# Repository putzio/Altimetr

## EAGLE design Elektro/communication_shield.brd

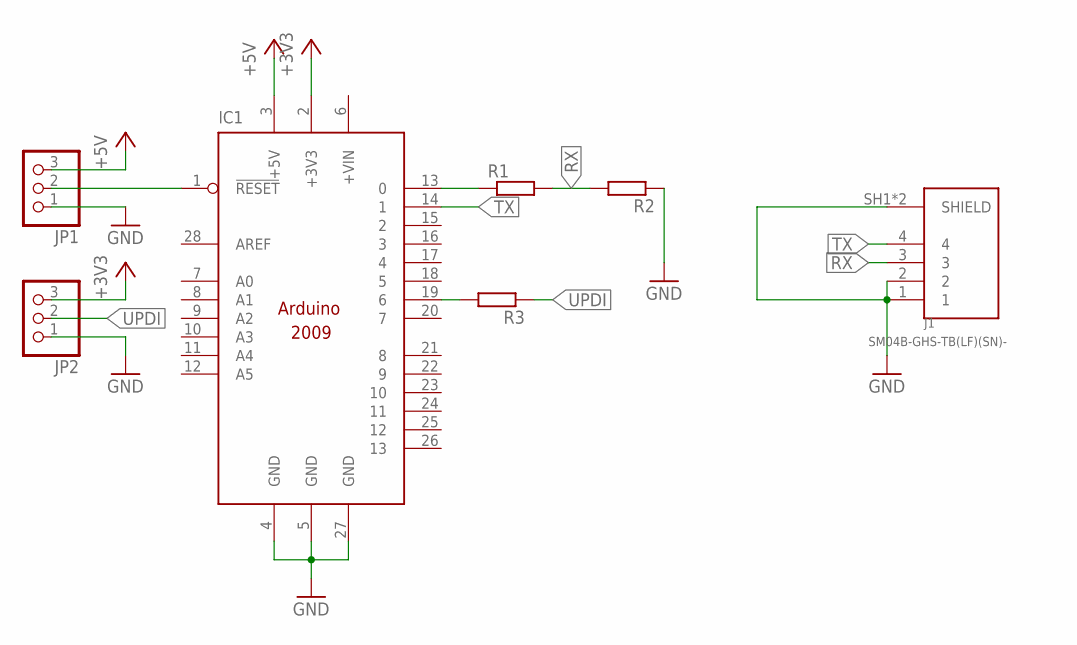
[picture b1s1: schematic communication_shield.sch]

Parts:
IC1: ARDUINO2009_10; ARDUINO2009
J1: SM04B-GHS-TB(LF)(SN)-; JST_SM04B-GHS-TB(LF)(SN)-
JP1, JP2: PINHD-1X3; 1X03
R1, R2, R3: R-EU_0204/7; 0204/7

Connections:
+3V3: IC1.2 (+3V3), JP2.3
+5V: IC1.3 (+5V), JP1.3
GND: IC1.4 (GND), IC1.5 (GND), IC1.27 (GND), J1.1, J1.2, J1.SH1 (SHIELD), J1.SH2 (SHIELD), JP1.1, JP2.1, R2.1
unnamed: IC1.19 (6), R3.2
unnamed: IC1.13 (0), R1.1
unnamed: IC1.1 (!RESET), JP1.2
RX: J1.3, R1.2, R2.2
TX: IC1.14 (1), J1.4
UPDI: JP2.2, R3.1

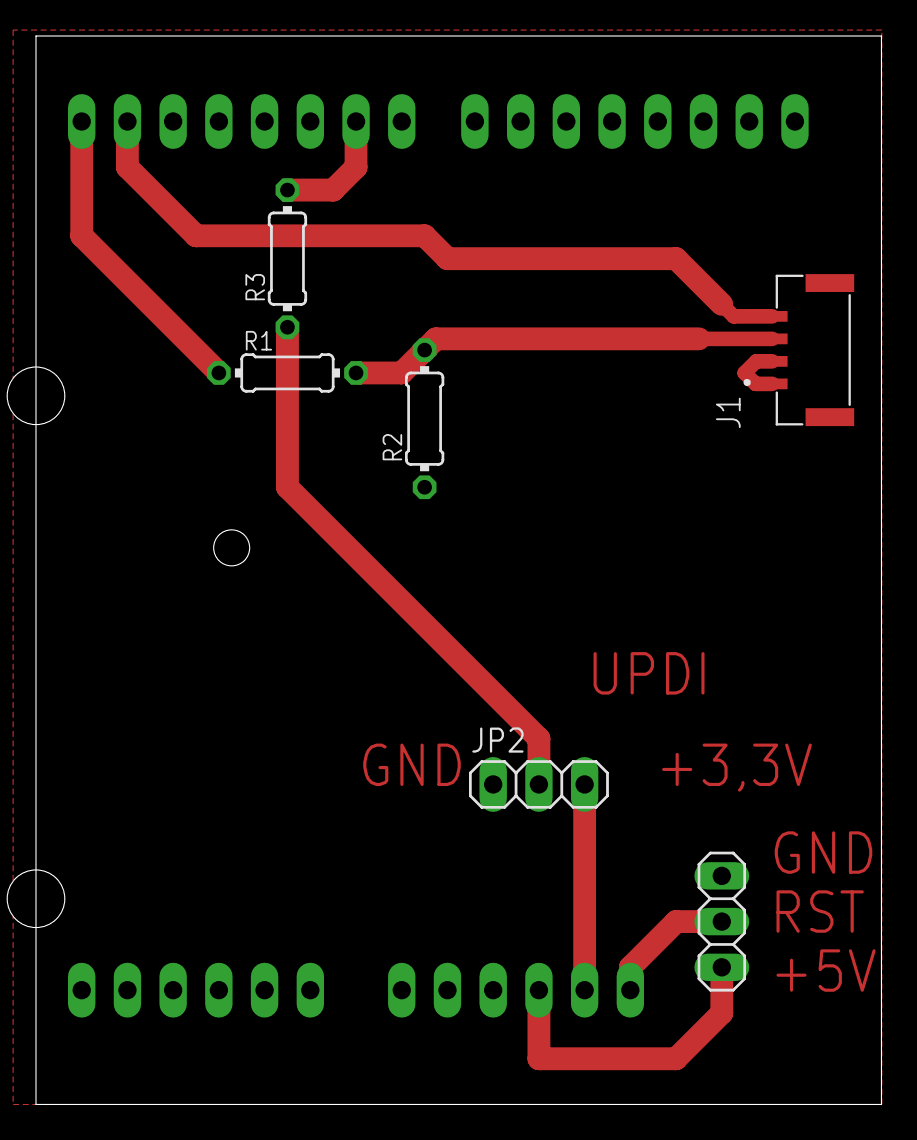
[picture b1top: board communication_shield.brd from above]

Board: 2 copper layers, 47.0 x 59.4 mm, 7 parts (1 on the bottom side), 9 nets.

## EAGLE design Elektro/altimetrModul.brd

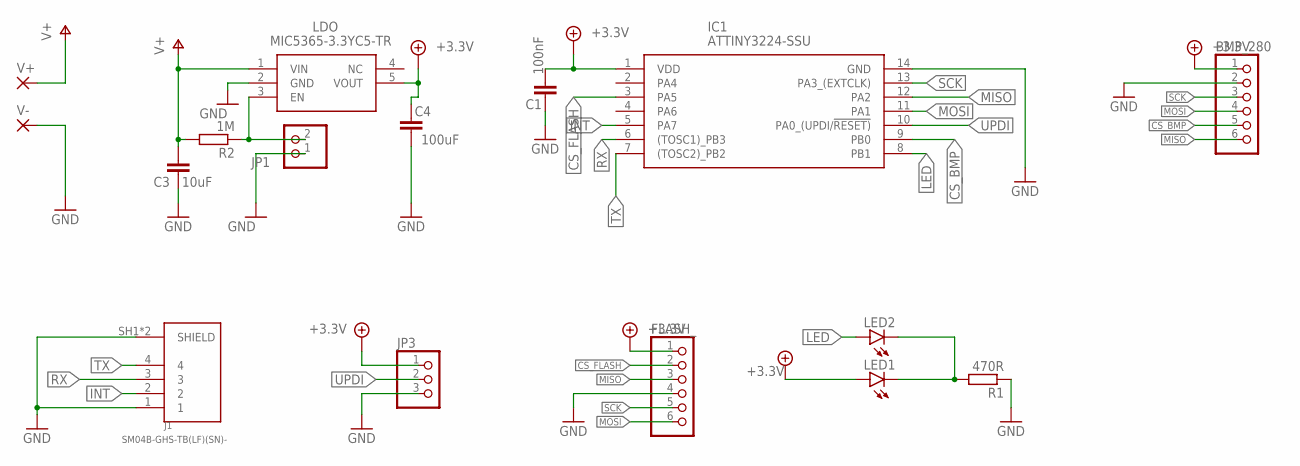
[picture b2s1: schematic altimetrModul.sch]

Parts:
BMP_280: PINHD-1X6; 1X06
C1: 100nF; C0805
C3: 10uF; C0805
C4: 100uF; C0805
FLASH_: PINHD-1X6; 1X06
IC1: ATTINY3224-SSU; SOIC127P600X175-14N
J1: SM04B-GHS-TB(LF)(SN)-; JST_SM04B-GHS-TB(LF)(SN)-
JP1: PINHD-1X2/90; 1X02/90
JP3: PINHD-1X3/90; 1X03/90
LDO: MIC5365-3.3YC5-TR; SOT65P210X110-5N
LED1, LED2: LEDCHIP-LED0805; CHIP-LED0805
R1: 470R; R0805
R2: 1M; R0805
V+: SMD2; SMD1,27-2,54
V-: SMD2; SMD1,27-2,54

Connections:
+3.3V: BMP_280.1, C1.1, C4.2, FLASH_.1, IC1.1 (VDD), JP3.1, LDO.5 (VOUT), LED1.A
CS_BMP: BMP_280.5, IC1.9 (PB0)
CS_FLASH: FLASH_.2, IC1.3 (PA5)
EN: JP1.2, LDO.3 (EN), R2.1
GND: BMP_280.2, C1.2, C3.1, C4.1, FLASH_.4, IC1.14 (GND), J1.1, J1.SH1 (SHIELD), J1.SH2 (SHIELD), JP1.1, JP3.3, LDO.2 (GND), R1.1, V-.1
INT: IC1.5 (PA7), J1.2
LED: IC1.8 (PB1), LED2.A
MISO: BMP_280.6, FLASH_.3, IC1.12 (PA2)
MOSI: BMP_280.4, FLASH_.6, IC1.11 (PA1)
unnamed: LED1.C, LED2.C, R1.2
RX: IC1.6 ((TOSC1)_PB3), J1.3
SCK: BMP_280.3, FLASH_.5, IC1.13 (PA3_(EXTCLK))
TX: IC1.7 ((TOSC2)_PB2), J1.4
UPDI: IC1.10 (PA0_(UPDI/!RESET)), JP3.2
V+: C3.2, LDO.1 (VIN), R2.2, V+.1

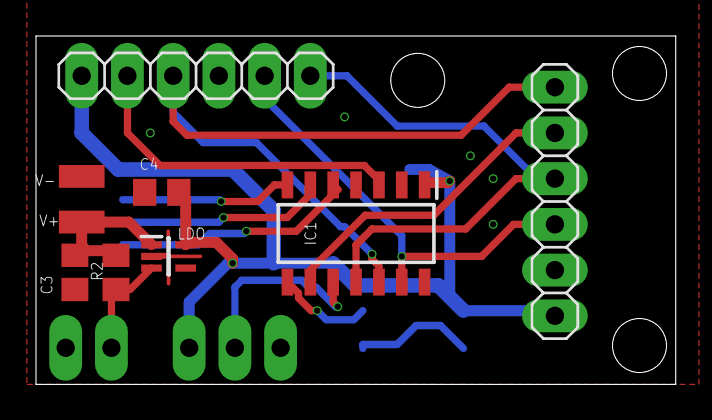
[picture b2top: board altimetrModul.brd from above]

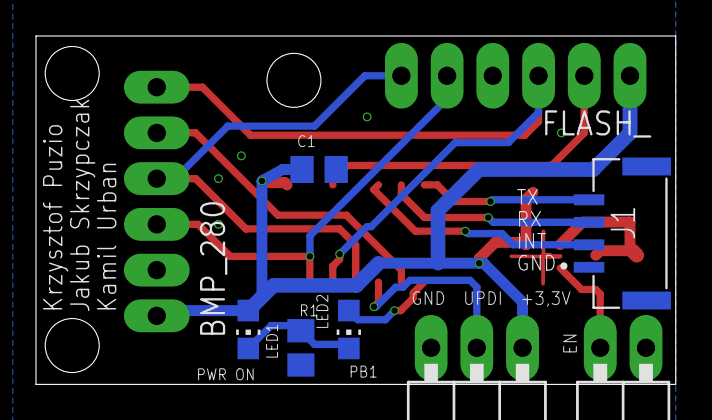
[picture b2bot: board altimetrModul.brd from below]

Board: 2 copper layers, 35.5 x 19.4 mm, 16 parts (7 on the bottom side), 15 nets.

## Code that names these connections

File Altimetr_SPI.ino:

//#include <Arduino.h>
//#include <SPI.h>
#include <avr/eeprom.h>
#include <Adafruit_BMP280.h>
#include <SPIMemory.h>
#include <SPI.h>
#include <avr/io.h>

// pinout
// CS -> write LOW to choose the salve
#define WRITE_PROTECTION 0  // WP - PA4
#define CS_FLASH 1          // PA5
#define SEND_DATA_UART_EN 3 // INT - PA7
#define RX 4                // PB3
#define TX 5                // PB2
#define LED 6               // PB1
#define CS_BMP 7            // PB0
#define UPDI 11             // PA0
#define MOSI 8              // PA1
#define MISO 9              // PA2
#define SCK 10              // PA3

#define SEA_LEVEL_HPA 1020.0
#define TIME_INTERVAL 1000 // ms
#define SEA_LEVEL_ADRESS 0x00 
#define START_ADRESS SEA_LEVEL_ADRESS

#define F_SPI 1000000 // 1 MHz -> the same frequency is required, so we take the lower one from BMP and set it to FLASH

SPIFlash *flash;
Adafruit_BMP280 bmp(CS_BMP, MOSI, MISO, SCK);

float initialHight;
uint64_t t = 0; // timer updated with millis()
bool flashOn = false;
uint32_t addr = 0x00;

float seaLevel;

void FlashBegin(bool *flashState = &flashOn)
{
  if (*flashState)
    Serial.println("Flash is already on");
  else
  {
    flash = new SPIFlash(CS_FLASH);
    flash->begin();
    *flashState = true;
  }
}
void FlashEnd(bool *flashState = &flashOn)
{
  if (*flashState)
  {
    SPI.end();
    delete flash;
    *flashState = false;
  }
  else
  {
    Serial.println("No flash object was used");
  }
}
// checks if the adress is empty
bool CheckAdress(uint32_t addr, bool flashState = flashOn)
{
  if (!flashState)
  {
    FlashBegin();
    if (Serial.available())
    {
      Serial.println("Initialised Flash in CheckAdress() function");
    }
  }
  int32_t val = flash->readLong(addr);
  if (!flashState) // this var has not changedif FlashBegin(), because it is not a *ptr
  {
    FlashEnd();
  }
  return (val == -1);
}

void FindEmptyAdress(volatile uint32_t *startingAdress, bool flashState = flashOn)
{
  if (!flashState)
  {
    FlashBegin();
    if (Serial.available())
    {
      Serial.println("Initialised Flash in FindEmptyAdress() function");
    }
  }

  uint32_t size = flash->getCapacity();
  while (1)
  {
    if (*startingAdress > size)
    {
      *startingAdress = 0;
      if (Serial.available())
      {
        Serial.println("FULL MEMORY");
      }
      break;
    }
    if (CheckAdress(*startingAdress))
      break;
    *startingAdress += 8;
  }
  if (!flashState) // this var has not changedif FlashBegin(), because it is not a *ptr
  {
    FlashEnd();
  }
}

void UartInit(uint16_t baud)
{
  Serial.begin(baud);
  while (!Serial.available() && !digitalRead(SEND_DATA_UART_EN))
    Serial.println("Waiting for connection...");
  if(Serial.available())
    Serial.println("Device connected");
}

void BMP280Init()
{
  if (!bmp.begin())
  {
    Serial.println(F("Could not find a valid BMP280 sensor, check wiring or "
                     "try a different address!"));
    while (1)
      delay(10);
  }
  /*
  Mode:           Normal -> 0xF4 [1:0] -> 11
  Oversampling:   Standard Resolution
  osrs_p:         x4 -> 0xF4 [4:2] -> 011
  osrs_t:         x1 -> 0xF4 [7:5] -> 001
  ODR[Hz]:        7.3
  RMS Noise[cm]:  6.4
  3 wire SPI:     false -> 0xF5[0] -> 0
  IIR filter:     4 -> 0xF5[4:2] -> 010?
  standby [ms]:   125 -> 0xF5 [7:5] -> 010
  */
  bmp.setSampling(Adafruit_BMP280::MODE_NORMAL,     /* Operating Mode. */
                  Adafruit_BMP280::SAMPLING_X1,     /* Temp. oversampling */
                  Adafruit_BMP280::SAMPLING_X4,     /* Pressure oversampling */
                  Adafruit_BMP280::FILTER_X4,       /* Filtering. */
                  Adafruit_BMP280::STANDBY_MS_125); /* Standby time. */
}

void setup()
{
  //Set all pins as OUTPUT:
  for (int i = 0; i < 11; i++) 
    pinMode(i, OUTPUT);
  
  pinMode(SEND_DATA_UART_EN, INPUT_PULLUP);
  UartInit(115200);
  FlashBegin();
  seaLevel = flash->readFloat(SEA_LEVEL_ADRESS);
  if(seaLevel<100.0)
    seaLevel = SEA_LEVEL_HPA; 
  FlashEnd();

  BMP280Init();  
  initialHight = bmp.readAltitude(seaLevel);
  if (Serial.available())
  {
    Serial.print("INITIAL HIGHT:\t");
    Serial.println(initialHight);
    Serial.print("TEMP:\t");
    Serial.println(bmp.readTemperature());
    Serial.print("PRESSURE:\t");
    Serial.println(bmp.readPressure());
  }

  // Flash
  FlashBegin();
  if (Serial.available())
  {
    Serial.println(flash->readLong(0x00));
  }
  FlashEnd();
  // if (Serial.available())
  // {
  //   Serial.print("Read Flash:\t");
  //   Serial.println(flash.readFloat(0x00));
  //   unsigned long size = flash.getCapacity();
  //   Serial.print("Flash Memory has ");
  //   Serial.p/rint(size);
  //   Serial.println(" bytes.");
  // }

  if (digitalRead(SEND_DATA_UART_EN))
  {
    // flash.eraseChip();
  }

  volatile uint32_t start;
  FindEmptyAdress(&start);
  if(Serial.available())
  {
    Serial.print("START ADDR:\t");
    Serial.println(start);
    Serial.print("How many measurements are stored:\t");
    Serial.println(start / 8);
  }
}

void loop()
{
  if (millis() - t > TIME_INTERVAL)
  {
    t = millis();

    if (!digitalRead(SEND_DATA_UART_EN))
    {
      addr = 0x04;
      FlashBegin();
      String recivedData = Serial.readString();
      if(recivedData != "-1")
        {
          if(recivedData.substring(0,3) =="#P:")
          {
            //Change Preassure
            float preassure =  recivedData.substring(3,recivedData.indexOf("&")).toFloat();
            flash->writeFloat(SEA_LEVEL_ADRESS, preassure);
          }
          if(recivedData.substring(0,3) =="###")
          {
            //Clear Flash
            flash->eraseChip();
          }
        }
      
      uint32_t flashCapacity = flash->getCapacity();
      uint32_t flashTime = 0,newFlashTime = 0;
      while(addr<flashCapacity)
      {
        newFlashTime =  flash->readLong(addr);
        if(flashTime>newFlashTime)
          Serial.println("end");//the new series of measurements has started
        flashTime = newFlashTime;
        // Serial.print("ADDR:\t");
        // Serial.print(addr, HEX);
        Serial.print("\t#t:\t");
        Serial.print(newFlashTime);
        addr += 4;
        Serial.print("\t&h:\t");
        Serial.print(flash->readFloat(addr));
        Serial.println("$");
        addr += 4;        
      }      
      Serial.println("END");      
    }
    else 
    {
      float hight = bmp.readAltitude(seaLevel); // - initialHight;
      // FlashBegin();
      //  flash->writeLong(addr, millis());
      addr += 4;
      // flash->writeFloat(addr, hight);
      addr += 4;
      // FlashEnd();
    }
  }
}
/*
To do:

->MIKRO
Czyszczenie flasha na komendę z UARTa
Wpisywanie do pamięci ciśnienia przez UART
kilka pomiarów na jednej pamięci

->PC
Komunikacja -> suma kontrolna, arbitraż
Wykres -> dopasowanie osi
Wysyłanie komendy kasowania i ustawienia ciśnienia
Obliczanie ciśnienia na poziomie morza na podstawie aktualnej wysokości i wskazań z BMP280 
*/

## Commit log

2022-03-31 Almost done?
2022-03-31 Electro begin
2022-04-03 Added Modules
2022-04-04 Added names
2022-04-10 Gerber generated in .zip
2022-04-10 Names on the bottom layer
2022-04-10 Gerberfile without pastemask
2022-04-11 Datasheets
2022-05-16 Some new functions to order UART etc.
2022-05-16 NEEDs TESTsgit add .! Sending correct frame (#t:xx&h:xx$), clear flash, preassure
2022-05-17 Create dokumentacja.docx
    Dokumentacja naszego projektu
2022-05-17 test
2022-05-17 Revert "test"
    This reverts commit 544f37aab3056d414bfdf0e580eea9a156e843a5.
2022-05-23 New Sltimetr_SPI directory and config.h file
2022-05-23 Code to test with a new ATTiny with more memory
2022-05-24 ATtiny 1624 changed to ATtiny 3224 (the memory size too small for all of the functionalities of the program
2022-06-02 Flash bugs fixed
2022-06-03 Connection works, hight changed to uint32_t (Long)
2022-06-03 Communication is fast and so smooth!
2022-06-12 Arduino communication shield, sending atmospheric preassure if asked
2022-06-12 Final version
2022-06-12 doku
